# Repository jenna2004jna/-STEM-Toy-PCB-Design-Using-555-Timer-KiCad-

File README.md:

# 🎵 STEM Toy PCB Design Using 555 Timer (KiCad)

📌 Project Overview

This project is a STEM Toy PCB designed using KiCad, based on a 555 Timer IC in astable mode.  
The circuit generates an audible tone using a buzzer and operates from a 3.2V power supply, making it suitable for low-power educational toys. This project helps beginners understand oscillators, RC timing, and PCB design.

---

## 🧠 Learning Objectives

- Understand 555 timer astable operation  
- Learn schematic → PCB → 3D view workflow in KiCad  
- Basic component placement & routing  
- Generate Gerber-ready PCB

---

## 🧩 Components Used

- Timer IC: 555 Timer  
- Resistor R1: 1 kΩ  
- Resistor R2: 10 kΩ  
- Capacitor C1: 1 µF  
- Capacitor C2: 100 uF  
- Buzzer: Active Buzzer  
- Power Supply: 3.2 V DC

---

## ⚙️ Working Principle

The 555 timer is configured in astable mode, continuously generating pulses. The resistors (1 kΩ and 10 kΩ) and the 1 µF capacitor set the oscillation frequency. The output (Pin 3) drives the buzzer to produce sound. The 100 uF capacitor improves noise stability. Powered from a 3.2 V battery for low-power operation.

---

## 🛠️ Design Tool

EDA Tool: KiCad

Design includes:
- Schematic design
- PCB layout
- 3D PCB visualization
- Single-layer PCB routing (or as designed)

---

## 🖼️ PCB Design Images

### 🔹 3D PCB View

### 🔹 PCB Top View

### 🔹 PCB Bottom View

---

## 📂 Repository Structure

STEM-Toy-555-Timer/  
│── Schematic/  
│   └── stem_toy_555.kicad_sch  
│── PCB/  
│   └── stem_toy_555.kicad_pcb  
│── Images/  
│   ├── image_1.png        ← 3D PCB view (rename to pcb_3d_view.png if desired)  
│   ├── image_2.png        ← PCB top view (rename to pcb_top_view.png if desired)  
│   └── image_3.png        ← PCB bottom view (rename to pcb_bottom_view.png if desired)  
│── README.md

Notes:
- Place your PNG files inside the Images/ folder.
- Use simple, lowercase names with no spaces. Example preferred names: pcb_3d_view.png, pcb_top_view.png, pcb_bottom_view.png

---

## 🔌 Power Requirements

- Input Voltage: 3.2 V DC  
- Battery powered, low current consumption

---

## 🎯 Applications

- STEM education kits  
- Beginner electronics learning  
- Sound-based toys  
- PCB design practice projects

---

## 🚀 Future Improvements

- Add LED indicator  
- Add potentiometer for tone control  
- Enclosure design for toy  
- Battery protection circuit

---

## 🔧 How to Export Images from KiCad (Quick)

1. Open your `.kicad_pcb`.  
2. View → 3D Viewer → File → Export → PNG → save as `image_1.png` (or `pcb_3d_view.png`).  
3. File → Plot → PNG → select Top Copper → save as `image_2.png` (or `pcb_top_view.png`).  
4. Repeat for Bottom Copper → save as `image_3.png` (or `pcb_bottom_view.png`).  
5. Create an `Images/` folder in your repo and move the PNG files there.  
6. Commit and push; GitHub will render them in this README.

Quick test (must work): If this README contains:
```

```
and `Images/image_1.png` exists in the repo, GitHub will display it.

---

## ⚠️ Common Mistakes (avoid)

- Wrong folder name (must be `Images`, not `images` or other)  
- Image not committed/pushed  
- Spaces in image file name  
- Wrong capitalization

---

## 👩‍💻 Author

Jenna  
Embedded Systems & PCB Design Enthusiast — KiCad | Embedded Systems | STEM Projects

---

## 📜 License

MIT — adapt and reuse freely. Please retain attribution when sharing.

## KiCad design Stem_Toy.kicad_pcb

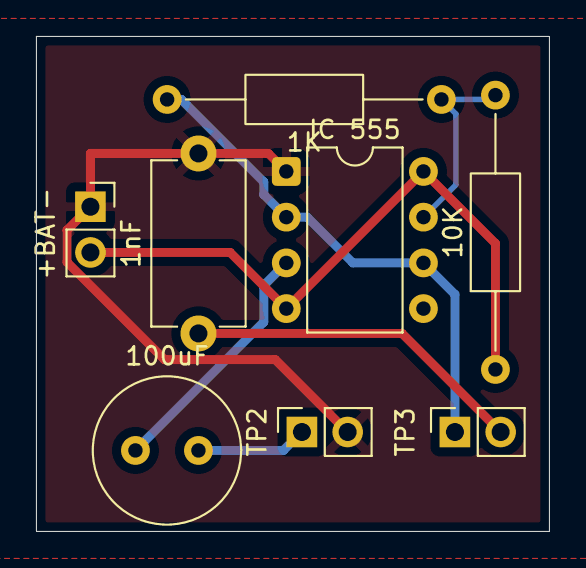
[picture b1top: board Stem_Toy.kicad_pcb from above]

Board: 2 copper layers, 28.5 x 27.5 mm, 8 parts (0 on the bottom side), 7 nets.

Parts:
1K: R; R_Axial_DIN0207_L6.3mm_D2.5mm_P15.24mm_Horizontal
1nF: C; C_Disc_D9.0mm_W5.0mm_P10.00mm
10K: 1k; R_Axial_DIN0207_L6.3mm_D2.5mm_P15.24mm_Horizontal
100uF: C_Polarized; C_Radial_D8.0mm_H11.5mm_P3.50mm
+BAT-: Battery; PinSocket_1x02_P2.54mm_Vertical
IC 555: NE555P; DIP-8_W7.62mm
TP2: TestPoint_2Pole; PinSocket_1x02_P2.54mm_Vertical
TP3: HUmanOUt; PinSocket_1x02_P2.54mm_Vertical

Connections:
/DIS: 1K.1, 10K.2, IC 555.7 (DIS)
/OUt: 100uF.1, IC 555.3 (Q)
/TR: 1K.2, IC 555.2 (TR), IC 555.6 (THR), TP3.1
GND: 1nF.2, +BAT-.1, IC 555.1 (GND), TP2.2
unnamed: 1nF.1, TP3.2
unnamed: 100uF.2, TP2.1
VCC: 10K.1, +BAT-.2, IC 555.4 (R), IC 555.8 (VCC)

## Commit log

2025-12-31 Add README for STEM Toy PCB project using 555 Timer
    This README provides an overview of a STEM Toy PCB project using a 555 Timer, including learning objectives, components used, working principles, and design tools. It also includes sections on reposi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
2025-12-31 Fix image paths in PCB design section
    Updated image paths in README for PCB design views.
